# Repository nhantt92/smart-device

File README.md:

# smart-home
## smart-home-project

### Touch pad 50x100-ttp223-8pad

### bluetooth-HC05-controller

### RF-Learnning-code-1relay 30A
- Nguồn cấp 12VDC

### RF-Learnning-code-1relay_30A-220V_input
- Nguồn cấp 220V, Module nguồn xung

### RF-Learnning-code-1relay_30A-220V_capacitor_input

- Nguồn cấp 220V, Nguồn hạ áp bằng tụ

### wifi-slack-1relay-controller-hw

-3D

- PCBA

- Product

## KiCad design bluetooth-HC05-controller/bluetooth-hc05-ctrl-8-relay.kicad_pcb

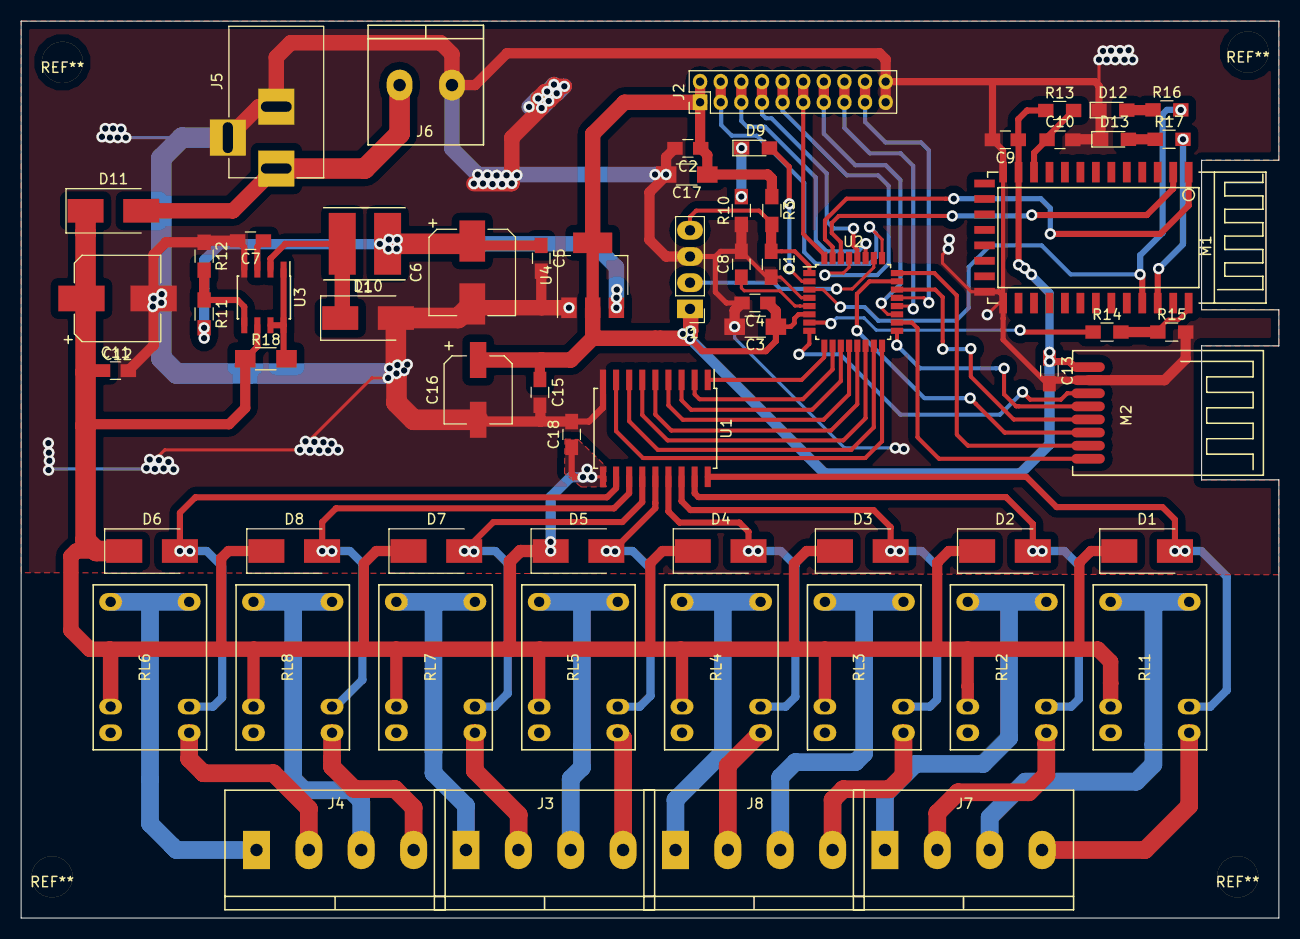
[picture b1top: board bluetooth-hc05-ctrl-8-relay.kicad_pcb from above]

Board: 2 copper layers, 122.0 x 87.0 mm, 63 parts (0 on the bottom side), 69 nets.

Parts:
C1, C2, C4, C5, C9, C10, C11, C13, C15, C18: 100n; C_0805_HandSoldering
C3, C17: 10uF; C_1206_HandSoldering
C6: CP1; CP_Elec_8x10
C7: 33p; C_0805_HandSoldering
C8: 1uF; C_0805_HandSoldering
C12: CP1; CP_Elec_8x10.5
C16: CP1; CP_Elec_6.3x7.7
D1, D2, D3, D4, D5, D6, D7, D8, D11: D_ALT; D_SMB_Handsoldering
D9, D12, D13: LED_ALT; LED_0805_HandSoldering
D10: D_Schottky; D_SMB_Handsoldering
J1: CONN_01X04; Header-4pin-2.54
J2: CONN_02X10; Pin_Header_Straight_2x10_Pitch2.00mm
J3, J4, J7, J8: CONN_01X04; Domino-5.08mm_4pol
J5: BARREL_JACK
J6: CONN_01X02; TerminalBlock_Pheonix_PT-5.08mm_2pol
L1: L_Small; Inductor_5.2x5.8x4.5
M1: Bluetooth-HC-05; bluetooth-HC-05
M2: nRF24L01-mini; nRF24L01-Mini
R3: 10k; R_0805_HandSoldering
R10, R16, R17: 470; R_0805_HandSoldering
R11, R12: 1k; R_0805_HandSoldering
R13, R15: 10K; R_0805_HandSoldering
R14: 1K; R_0805_HandSoldering
R18: 0.15; R_1206_HandSoldering
RL1, RL2, RL3, RL4, RL5, RL6, RL7, RL8: RELAY-HK4100
U1: ULN2803A; SOIC-18W_7.5x11.6mm_Pitch1.27mm
U2: STM8S003K3T; LQFP-32_7x7mm_Pitch0.8mm
U3: MC34063; SOIC-8_3.9x4.9mm_Pitch1.27mm
U4: ASM1117; SOT-223

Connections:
+3V3: C2.1, C3.1, C4.1, C9.1, C13.1, C15.1, C16.1, C17.1, J1.1, J2.1, J2.2, M1.12, M2.1, R3.1, R13.1, U2.6, U4.2, U4.4
+5V: C5.1, C6.1, L1.1, R11.2, U4.3
+12V: C11.1, C12.1, C18.1, D1.1, D2.1, D3.1, D4.1, D5.1, D6.1, D7.1, D8.1, D11.1, R18.1, RL1.2, RL2.2, RL3.2, RL4.2, RL5.2, RL6.2, RL7.2, RL8.2, U1.10, U3.6
/BRST: C10.1, M1.11, R13.2
/CE: M2.3, U2.8
/CMD: R14.1, U2.7
/CO1: J7.4, RL1.5
/CO2: J7.2, RL2.5
/CO3: J8.4, RL3.5
/CO4: J8.2, RL4.5
/CO5: J3.4, RL5.5
/CO6: J3.2, RL7.5
/CO7: J4.4, RL8.5
/CO8: J4.2, RL6.5
/IRQ: M2.8, U2.18
/KEY1: J2.3, J2.4, U2.25
/KEY2: J2.5, J2.6, U2.27
/KEY3: J2.7, J2.8, U2.28
/KEY4: J2.9, J2.10, U2.29
/KEY5: J2.11, J2.12, U2.32
/KEY6: J2.13, J2.14, U2.19
/KEY7: J2.15, J2.16, U2.20
/KEY8: J2.17, J2.18, U2.21
/MISO: M2.7, U2.24
/MOSI: M2.6, U2.23
/NO1: J7.3, RL1.3
/NO2: J7.1, RL2.3
/NO3: J8.3, RL3.3
/NO4: J8.1, RL4.3
/NO5: J3.3, RL5.3
/NO6: J3.1, RL7.3
/NO7: J4.3, RL8.3
/NO8: J4.1, RL6.3
/NRST: C1.1, J1.4, R3.2, U2.1
/NSS: M2.4, U2.17
/OUT1: U1.1, U2.9
/OUT2: U1.2, U2.10
/OUT3: U1.3, U2.11
/OUT4: U1.4, U2.12
/OUT5: U1.5, U2.13
/OUT6: U1.6, U2.14
/OUT7: U1.7, U2.15
/OUT8: U1.8, U2.16
/RL1: D1.2, RL1.1, U1.18
/RL2: D2.2, RL2.1, U1.17
/RL3: D3.2, RL3.1, U1.16
/RL4: D4.2, RL4.1, U1.15
/RL5: D5.2, RL5.1, U1.14
/RL6: D7.2, RL7.1, U1.13
/RL7: D8.2, RL8.1, U1.12
/RL8: D6.2, RL6.1, U1.11
/RXD: M1.1, U2.31
/SCK: M2.5, U2.22
/STATE: M1.31, R16.2, U2.3
/SWIM: J1.2, U2.26
/TXD: M1.2, U2.30
/VIN: D11.2, J5.1, J6.2
GND: C1.2, C2.2, C3.2, C4.2, C5.2, C6.2, C7.2, C8.2, C9.2, C10.2, C11.2, C12.2, C13.2, C15.2, C16.2, C17.2, C18.2, D10.2, D12.1, D13.1, J1.3, J2.19, J2.20, J5.2, J5.3, J6.1, M1.13, M1.21, M1.22, M2.2, R10.1, R12.1, R15.2, U1.9, U2.4, U3.4, U4.1
unnamed: C7.1, U3.3
unnamed: C8.1, U2.5
unnamed: D9.1, R10.2
unnamed: D9.2, U2.2
unnamed: D10.1, L1.2, U3.2
unnamed: D12.2, R16.1
unnamed: D13.2, R17.1
unnamed: M1.32, R17.2
unnamed: M1.34, R14.2, R15.1
unnamed: R11.1, R12.2, U3.5
unnamed: R18.2, U3.1, U3.7, U3.8

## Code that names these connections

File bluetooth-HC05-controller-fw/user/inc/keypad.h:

#ifndef __KEYPAD_H
#define __KEYPAD_H

/* Includes ------------------------------------------------------------------*/
#include "stm8s.h"
#include "stm8s_gpio.h"
#include "timerTick.h"

#define KEY_PORT1 GPIOD
#define KEY_PORT2 GPIOC
#define KEY1 GPIO_PIN_0
#define KEY2 GPIO_PIN_2
#define KEY3 GPIO_PIN_3
#define KEY4 GPIO_PIN_4
#define KEY5 GPIO_PIN_7
#define KEY6 GPIO_PIN_2
#define KEY7 GPIO_PIN_3
#define KEY8 GPIO_PIN_4

#define KEY1_In() GPIO_ReadInputPin(KEY_PORT1, KEY1)
#define KEY2_In() GPIO_ReadInputPin(KEY_PORT1, KEY2)
#define KEY3_In() GPIO_ReadInputPin(KEY_PORT1, KEY3)
#define KEY4_In() GPIO_ReadInputPin(KEY_PORT1, KEY4)
#define KEY5_In() GPIO_ReadInputPin(KEY_PORT1, KEY5)
#define KEY6_In() GPIO_ReadInputPin(KEY_PORT2, KEY6)
#define KEY7_In() GPIO_ReadInputPin(KEY_PORT2, KEY7)
#define KEY8_In() GPIO_ReadInputPin(KEY_PORT2, KEY8)

#define NUM_OF_SAMPLE_KEY   10
#define NUM_KEY 8

typedef enum{
  TP_LEFT1 = 0,
  TP_RIGHT1 = 1,
  TP_LEFT2 = 2,
  TP_RIGHT2 = 3,
}TP_NAME;

typedef enum {
  TP_RELEASE = 0,
  TP_PRESS,
}TP_EVENT;

typedef struct {
  uint8_t pressed;
  uint8_t press; 
  uint8_t waitRelease;
  uint8_t cnt;
}TP_EXT;

typedef struct {
  uint8_t name;
  TP_EXT ext[NUM_KEY];
  TIME tick;
}TP_STRUCT;

void touch_pad_init(void);
void touch_get(uint8_t port_id);
uint8_t tp_get(uint8_t id);
void tp_process(void);
void touch_pad_manager(void);


#endif /* __KEYPAD_H */

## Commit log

2017-11-07 upload hw
2017-11-08 Init fw bluetooth HC05 - controller
2017-11-08 upload hw rf-learn-command-1relay
2017-11-08 upload hw project rf-learn-command-1relay-220V
2017-11-08 upload project rf-learn-command-1relay-220v-capacitor
2017-11-09 add wifi-slack-controller
2017-11-09 add wifi-slack-1relay-controller-fw
2017-11-10 upload fw rf-learnning
2017-11-10 fix fw remote EV1527
2017-12-01 add rf-fixcode
2017-12-16 complete rf-fix-code-2-relay-hw
2017-12-26 upload project pcb rf-4-channel
